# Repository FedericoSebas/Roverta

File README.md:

## Rover de Exploración

Este proyecto se centra en un rover de exploración que se divide en dos secciones principales: el controlador de motores y la estación meteorológica.

### Controlador de Motores

El controlador de motores es responsable de la locomoción del rover. Permite al rover moverse y navegar por su entorno.

### Estación Meteorológica

La estación meteorológica es controlada por un ESP32 y utiliza varios sensores para recopilar datos sobre el entorno. Los sensores incluyen:

- **Fotodiodo y LDR (Resistencia Dependiente de la Luz)**: Estos son sensores analógicos que miden la intensidad de la luz. El fotodiodo es sensible a la luz visible y cercana al infrarrojo, mientras que el LDR cambia su resistencia en función de la cantidad de luz que recibe.

- **DHT22**: Este es un sensor digital de temperatura y humedad. Puede medir temperaturas entre -40 y 80 grados Celsius, y humedad relativa entre 0 y 100%.

- **BMP280**: Este es un sensor digital que puede medir la presión barométrica y la temperatura. La presión barométrica se puede utilizar para calcular la altitud, lo que puede ser útil para determinar la posición del rover.

## Software

El software proporcionado incluye la biblioteca MQTT creada por nuestro equipo, así como bibliotecas individuales para cada dispositivo que se relacionan con MQTT. Esto se debe a que cada dispositivo tiene una callback para topicos y suscripciones, por lo que es más claro qué topico está relacionado con cada dispositivo.

Esperamos que este proyecto sea de su interés y le invitamos a explorar más a fondo el código y las funcionalidades del rover.

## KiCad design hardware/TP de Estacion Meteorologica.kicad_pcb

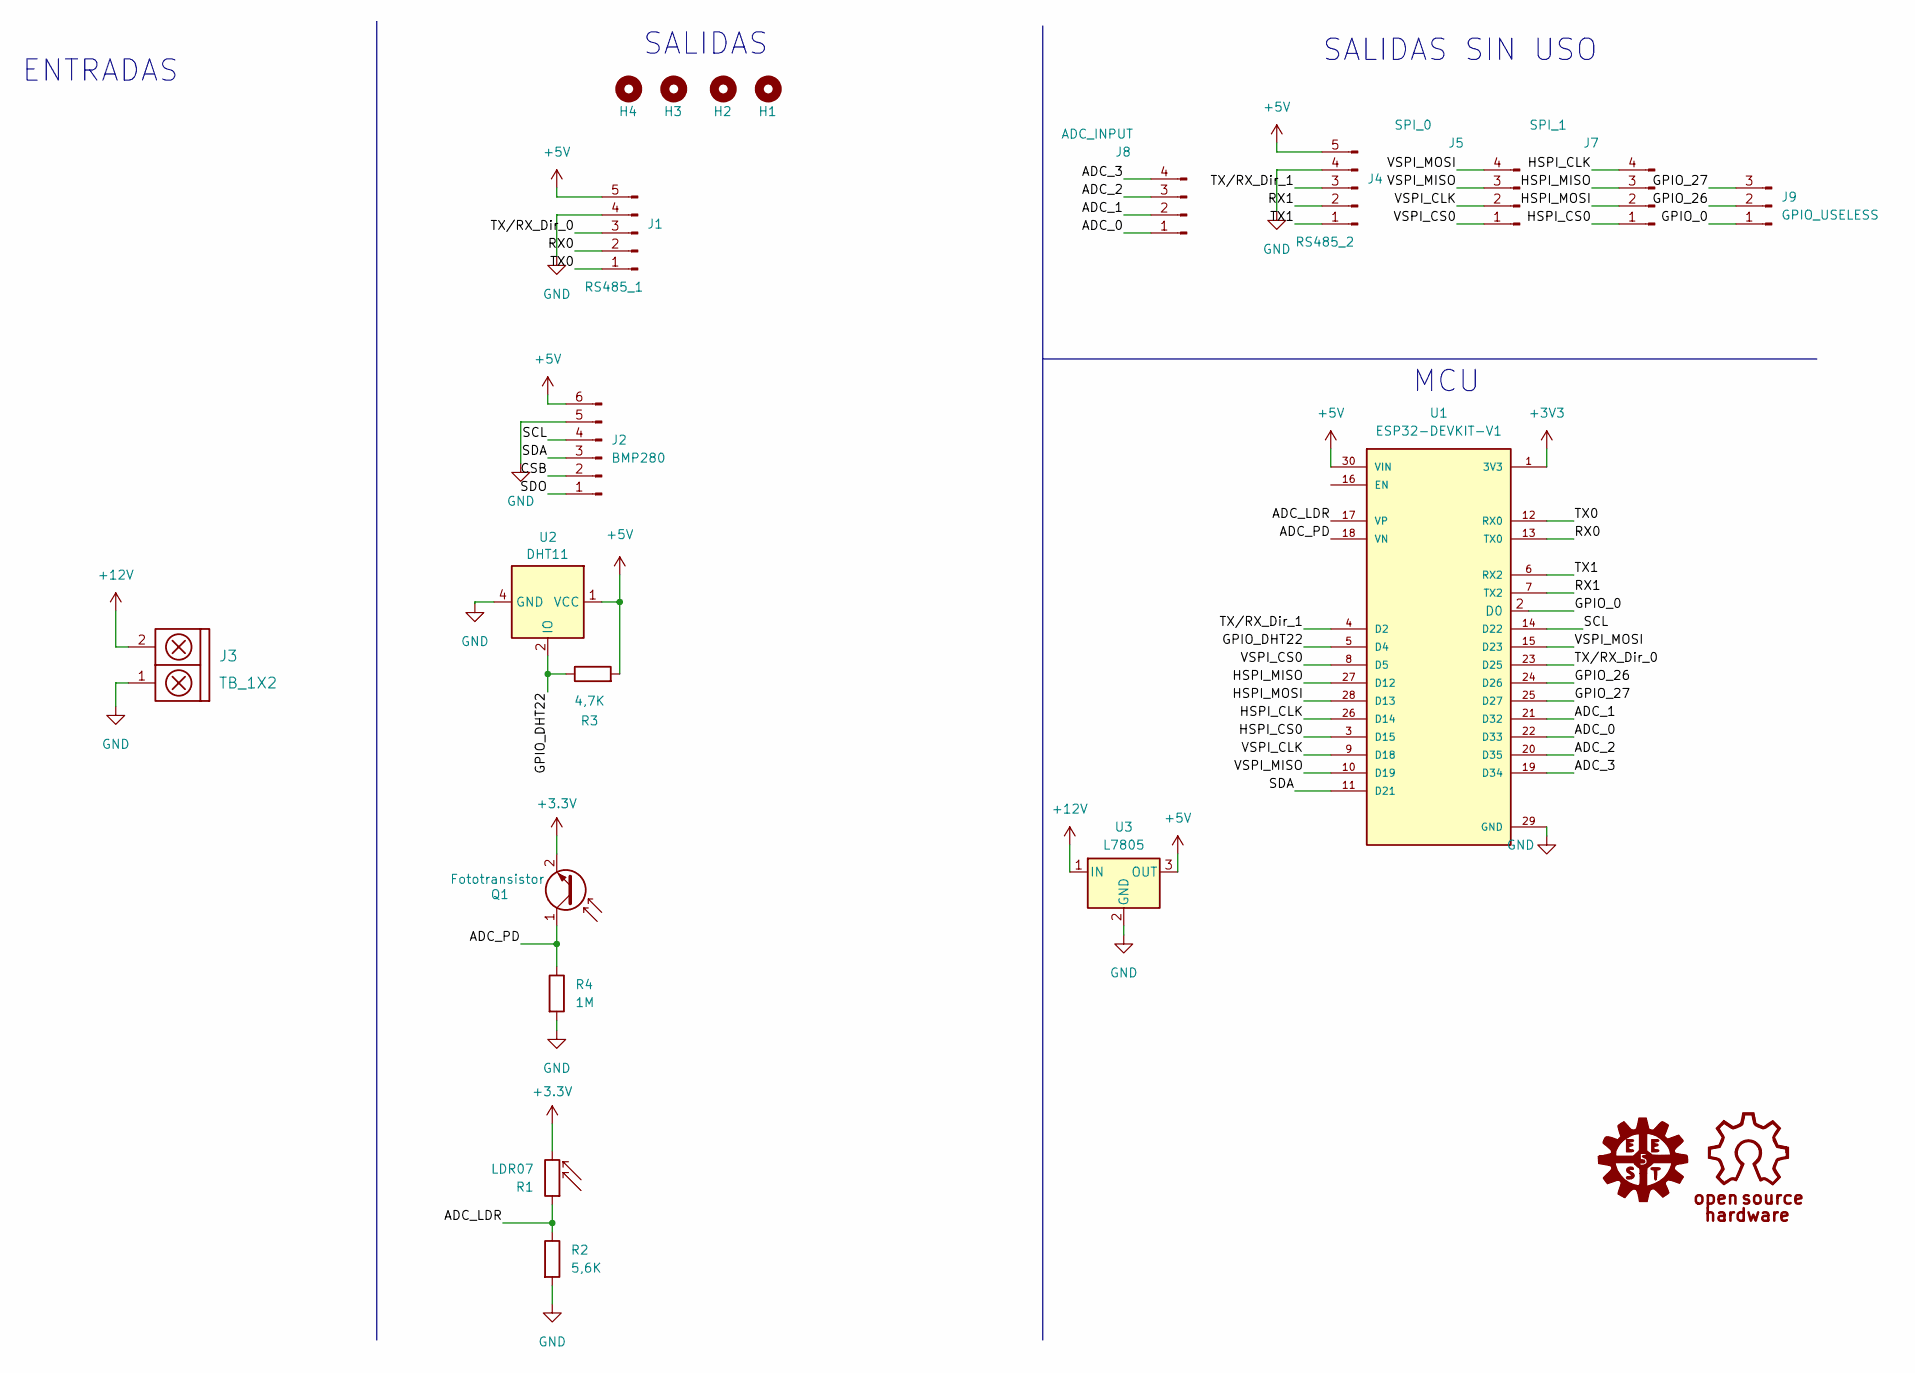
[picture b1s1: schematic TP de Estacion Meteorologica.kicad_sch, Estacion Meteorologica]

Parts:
H1, H2, H3, H4: Mounting_Hole; MountingHole_3mm
J1: RS485_1; PinSocket_1x05_P2.54mm_Vertical
J2: BMP280; PinSocket_1x06_P2.54mm_Vertical
J3: TB_1X2; BORNERA2_AZUL
J4: RS485_2; PinSocket_1x05_P2.54mm_Vertical
J5: SPI_0; PinSocket_1x04_P2.54mm_Vertical
J7: SPI_1; PinSocket_1x04_P2.54mm_Vertical
J8: ADC_INPUT; PinSocket_1x04_P2.54mm_Vertical
J9: GPIO_USELESS; PinSocket_1x03_P2.54mm_Vertical
Q1: Fototransistor; LED_D3.0mm_FlatTop
R1: LDR07; R_LDR_5.0x4.1mm_P3mm_Vertical
R2: 5,6K; R_Axial_DIN0207_L6.3mm_D2.5mm_P10.16mm_Horizontal
R3: 4,7K; R_Axial_DIN0207_L6.3mm_D2.5mm_P10.16mm_Horizontal
R4: 1M; R_Axial_DIN0207_L6.3mm_D2.5mm_P10.16mm_Horizontal
U1: ESP32-DEVKIT-V1; MODULE_ESP32_DEVKIT_V1; PARTREV N/A
U2: DHT11; Aosong_DHT11_5.5x12.0_P2.54mm
U3: L7805; TO-220-3_Horizontal_TabDown

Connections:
+5V: J1.5, J2.6, J4.5, R3.2, U1.30 (VIN), U2.1 (VCC), U3.3 (OUT)
+12V: J3.2, U3.1 (IN)
/ADC_0: J8.1, U1.22 (D33)
/ADC_1: J8.2, U1.21 (D32)
/ADC_2: J8.3, U1.20 (D35)
/ADC_3: J8.4, U1.19 (D34)
/ADC_LDR: R1.1, R2.1, U1.17 (VP)
/ADC_PD: Q1.1 (C), R4.1, U1.18 (VN)
/CSB: J2.2
/GPIO_0: J9.1, U1.2 (D0)
/GPIO_26: J9.2, U1.24 (D26)
/GPIO_27: J9.3, U1.25 (D27)
/GPIO_DHT22: R3.1, U1.5 (D4), U2.2 (IO)
/HSPI_CLK: J7.4, U1.26 (D14)
/HSPI_CS0: J7.1, U1.3 (D15)
/HSPI_MISO: J7.3, U1.27 (D12)
/HSPI_MOSI: J7.2, U1.28 (D13)
/RX0: J1.2, U1.13 (TX0)
/RX1: J4.2, U1.7 (TX2)
/SCL: J2.4, U1.14 (D22)
/SDA: J2.3, U1.11 (D21)
/SDO: J2.1
/TX0: J1.1, U1.12 (RX0)
/TX1: J4.1, U1.6 (RX2)
/TX/RX_Dir_0: J1.3, U1.23 (D25)
/TX/RX_Dir_1: J4.3, U1.4 (D2)
/VSPI_CLK: J5.2, U1.9 (D18)
/VSPI_CS0: J5.1, U1.8 (D5)
/VSPI_MISO: J5.3, U1.10 (D19)
/VSPI_MOSI: J5.4, U1.15 (D23)
GND: J1.4, J2.5, J3.1, J4.4, R2.2, R4.2, U1.29 (GND), U2.4 (GND), U3.2 (GND)

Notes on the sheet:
ENTRADAS
SALIDAS
MCU
SALIDAS SIN USO

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
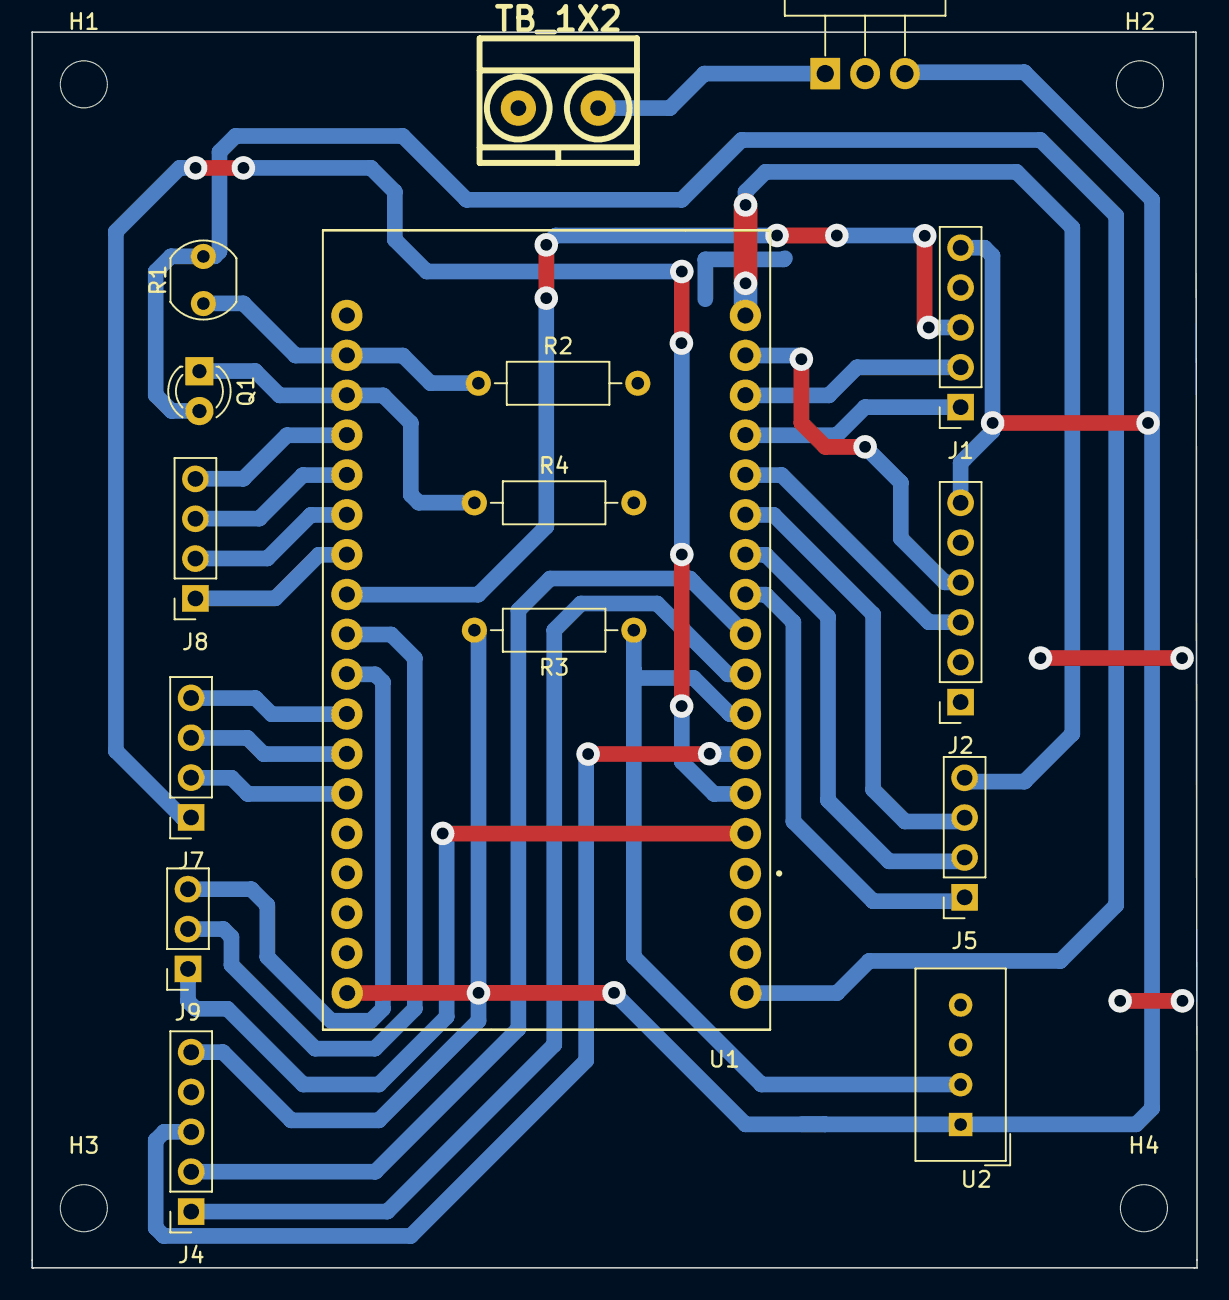
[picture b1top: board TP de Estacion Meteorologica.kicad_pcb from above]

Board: 2 copper layers, 74.2 x 78.8 mm, 20 parts (0 on the bottom side), 30 nets.

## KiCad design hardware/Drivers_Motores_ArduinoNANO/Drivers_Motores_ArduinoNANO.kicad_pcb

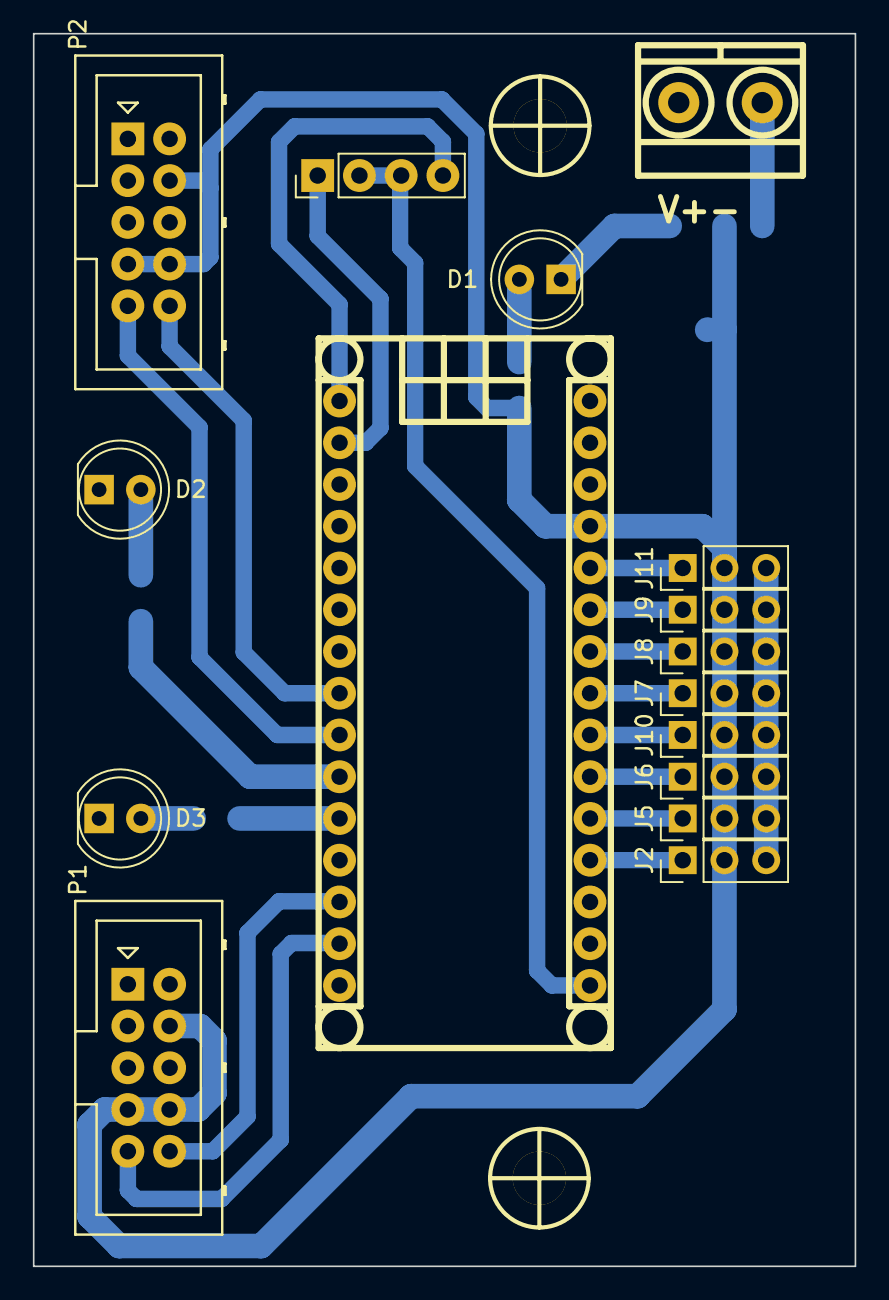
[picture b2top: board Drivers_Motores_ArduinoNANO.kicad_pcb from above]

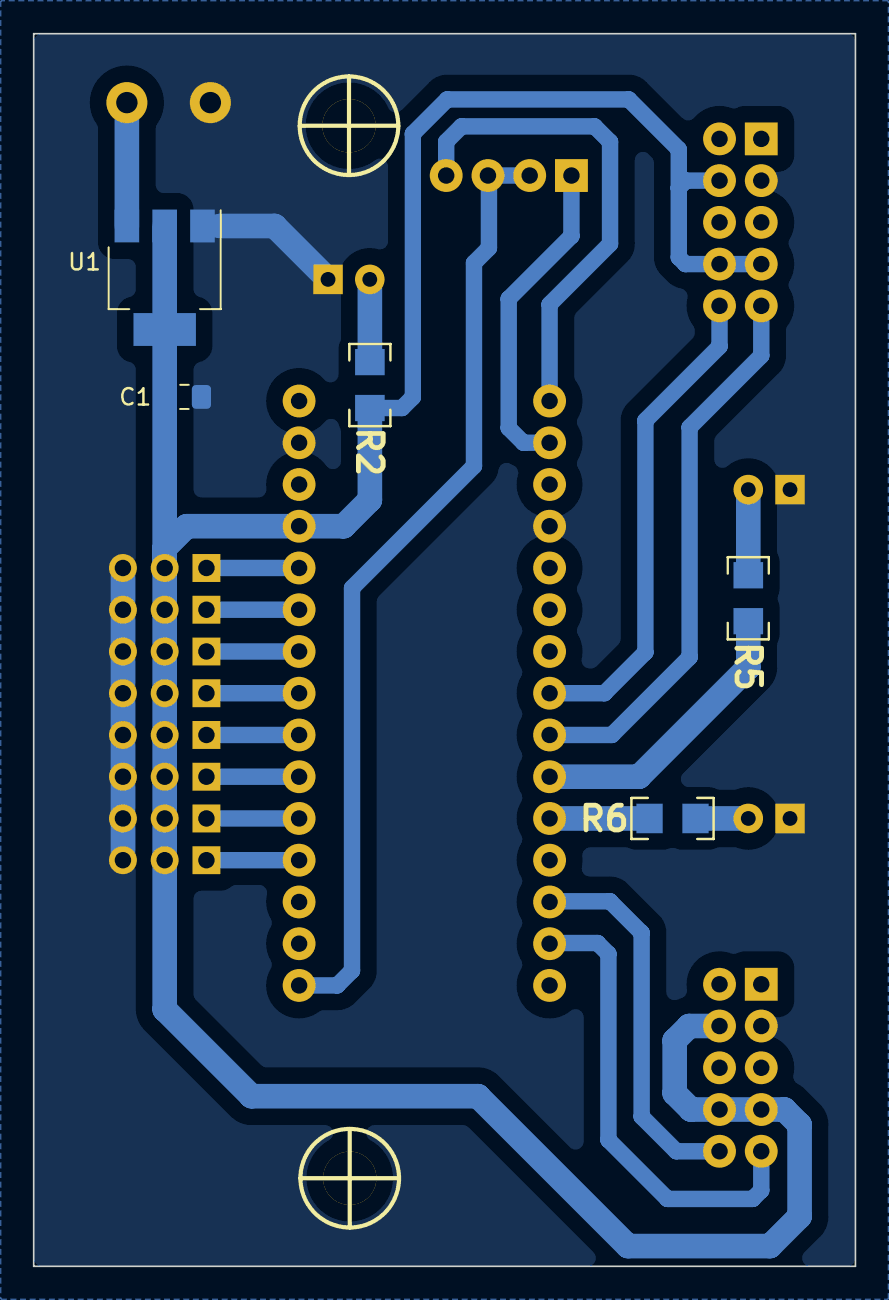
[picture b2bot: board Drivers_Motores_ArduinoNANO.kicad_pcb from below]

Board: 2 copper layers, 50.0 x 75.0 mm, 23 parts (5 on the bottom side), 23 nets.

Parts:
C1: 1uF; C_0805_2012Metric_Pad1.18x1.45mm_HandSolder
D1, D2, D3: LED; LED_D5.0mm
H1, H2: Mounting_Hole; Separador_M3_5mm
J1: V+-; BORNERA2_AZUL
J2, J5, J6, J7, J8, J9, J10, J11: Conn; PinHeader_1x03_P2.54mm_Vertical
J3: RS485; PinHeader_1x04_P2.54mm_Vertical
J4: Arduino_Nano_Header; arduino_nano_header
P1, P2: HEADER_02X05; Header_2x05x2.54mm_Vertical
R2, R6: 1K; R_1206
R5: 220; R_1206
U1: AMS1117-5.0; SOT-223-3_TabPin2

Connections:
+5V: C1.1, J2.2, J4.27 (5V), J5.2, J6.2, J7.2, J8.2, J9.2, J10.2, J11.2, P1.4, P1.7, P1.8, P2.4, P2.7, P2.8, R2.2, U1.2 (VO)
/1: J2.1, J4.19 (A0)
/2: J4.20 (A1), J5.1
/3: J4.21 (A2), J6.1
/4: J4.22 (A3), J10.1
/5: J4.23 (A4), J7.1
/6: J4.24 (A5), J8.1
/7: J4.25 (A6), J9.1
/8: J4.26 (A7), J11.1
/DERE: J3.2, J3.3, J4.16 (SCK/D13)
/LED_1: J4.11 (D8/ICP), R6.1
/LED_2: J4.10 (D7/AIN1), R5.1
/M1A: J4.13 (D10/SS), P1.10
/M1B: J4.14 (D11/MOSI), P1.9
/M2A: J4.8 (D5/T1), P2.10
/M2B: J4.9 (D6/AIN0), P2.9
/Rx: J3.1, J4.2 (D0/RX)
/Tx: J3.4, J4.1 (D1/TX)
GND: C1.2, D1.1 (K), D2.1 (K), D3.1 (K), J1.2, J2.3, J4.4 (GND), J4.29 (GND), J5.3, J6.3, J7.3, J8.3, J9.3, J10.3, J11.3, P1.3, P2.3, U1.1 (GND)
unnamed: D1.2 (A), R2.1
unnamed: D2.2 (A), R5.2
unnamed: D3.2 (A), R6.2
VCC: J1.1, U1.3 (VI)

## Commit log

2023-08-16 init project
2023-08-28 Creacion de los archivos para la placa de drivers
2023-08-29 weather station and mqtt src code for esp32
2023-08-29 pirmera parte de la llanta
2023-09-22 Archivos para el programa
2023-09-25 Diseño driver motor shield
2023-09-25 add enum magnitudes in Sensor.h
2023-10-18 Nuevo PCb
2023-11-24 ready to merge
2023-11-24 replace pdfs to pngs
2023-11-24 change quality of pngs
2023-11-24 error in commits from weather station branch
